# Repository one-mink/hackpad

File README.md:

# Hackpad
A macropad.

CAD

Schematics

PCB

Case

BOM:
    5x Cherry MX Switches
    5x DSA Keycaps
    2x WS2812B LEDs
    2x EC11 Rotary Encoder
    1x XIAO RP2040
    1x Case (2 printed parts)
    4x M3x5mx4mm heatset inserts

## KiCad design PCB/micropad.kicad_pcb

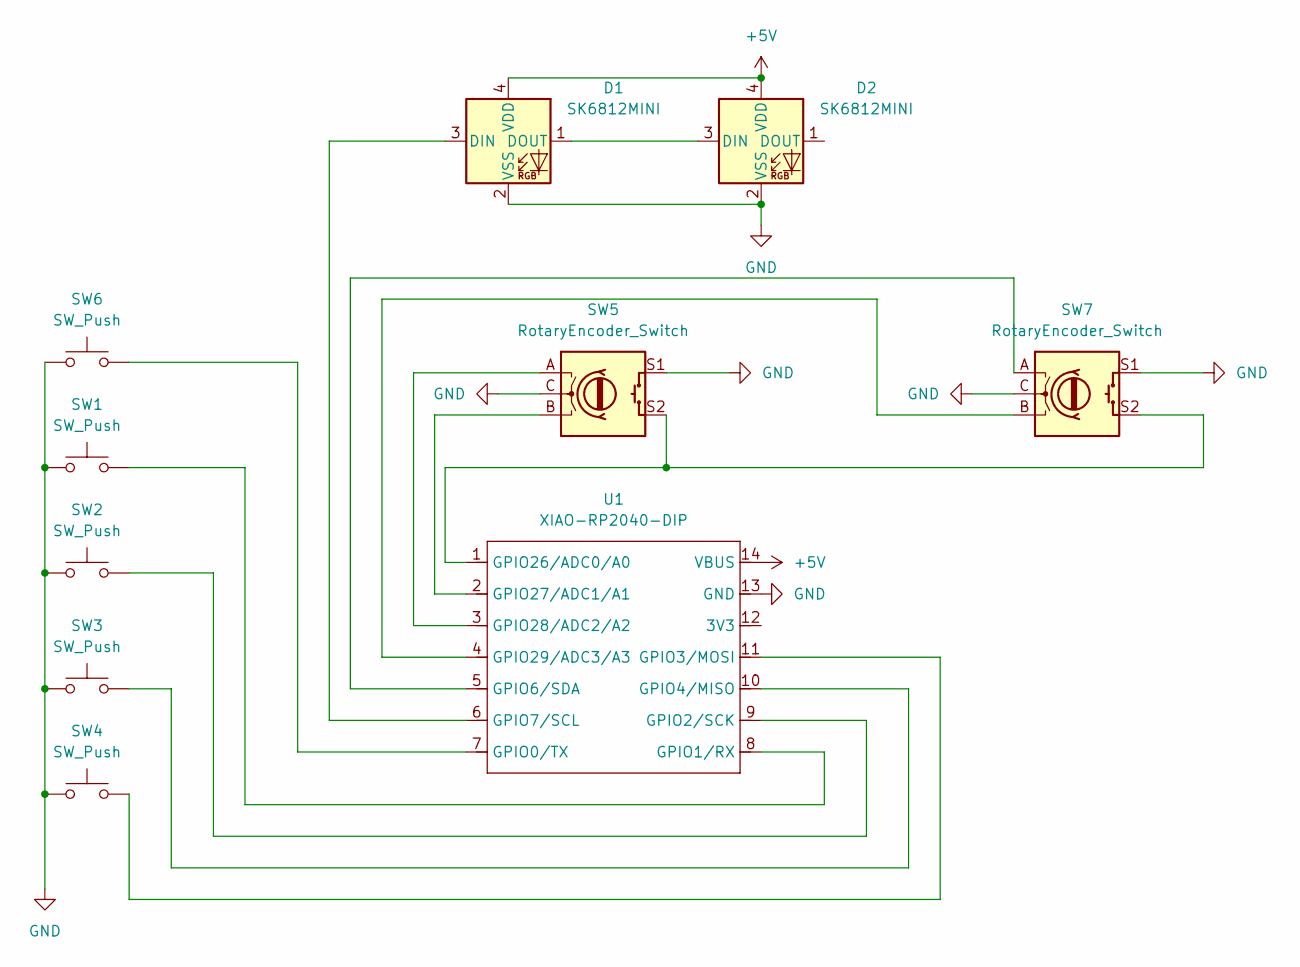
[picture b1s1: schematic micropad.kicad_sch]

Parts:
D1, D2: SK6812MINI; LED_SK6812MINI_PLCC4_3.5x3.5mm_P1.75mm
SW1, SW2, SW3, SW4, SW6: SW_Push; SW_Cherry_MX_1.00u_PCB
SW5, SW7: RotaryEncoder_Switch; RotaryEncoder_Alps_EC11E-Switch_Vertical_H20mm
U1: XIAO-RP2040-DIP

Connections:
+5V: D1.4 (VDD), D2.4 (VDD), U1.14 (VBUS)
GND: D1.2 (VSS), D2.2 (VSS), SW1.1, SW2.1, SW3.1, SW4.1, SW5.C, SW5.S1, SW6.1, SW7.C, SW7.S1, U1.13 (GND)
unnamed: D1.3 (DIN), U1.6 (GPIO7/SCL)
unnamed: D1.1 (DOUT), D2.3 (DIN)
unnamed: SW6.2, U1.7 (GPIO0/TX)
unnamed: SW1.2, U1.8 (GPIO1/RX)
unnamed: SW2.2, U1.9 (GPIO2/SCK)
unnamed: SW4.2, U1.11 (GPIO3/MOSI)
unnamed: SW3.2, U1.10 (GPIO4/MISO)
unnamed: SW7.A, U1.5 (GPIO6/SDA)
unnamed: SW5.S2, SW7.S2, U1.1 (GPIO26/ADC0/A0)
unnamed: SW5.B, U1.2 (GPIO27/ADC1/A1)
unnamed: SW5.A, U1.3 (GPIO28/ADC2/A2)
unnamed: SW7.B, U1.4 (GPIO29/ADC3/A3)

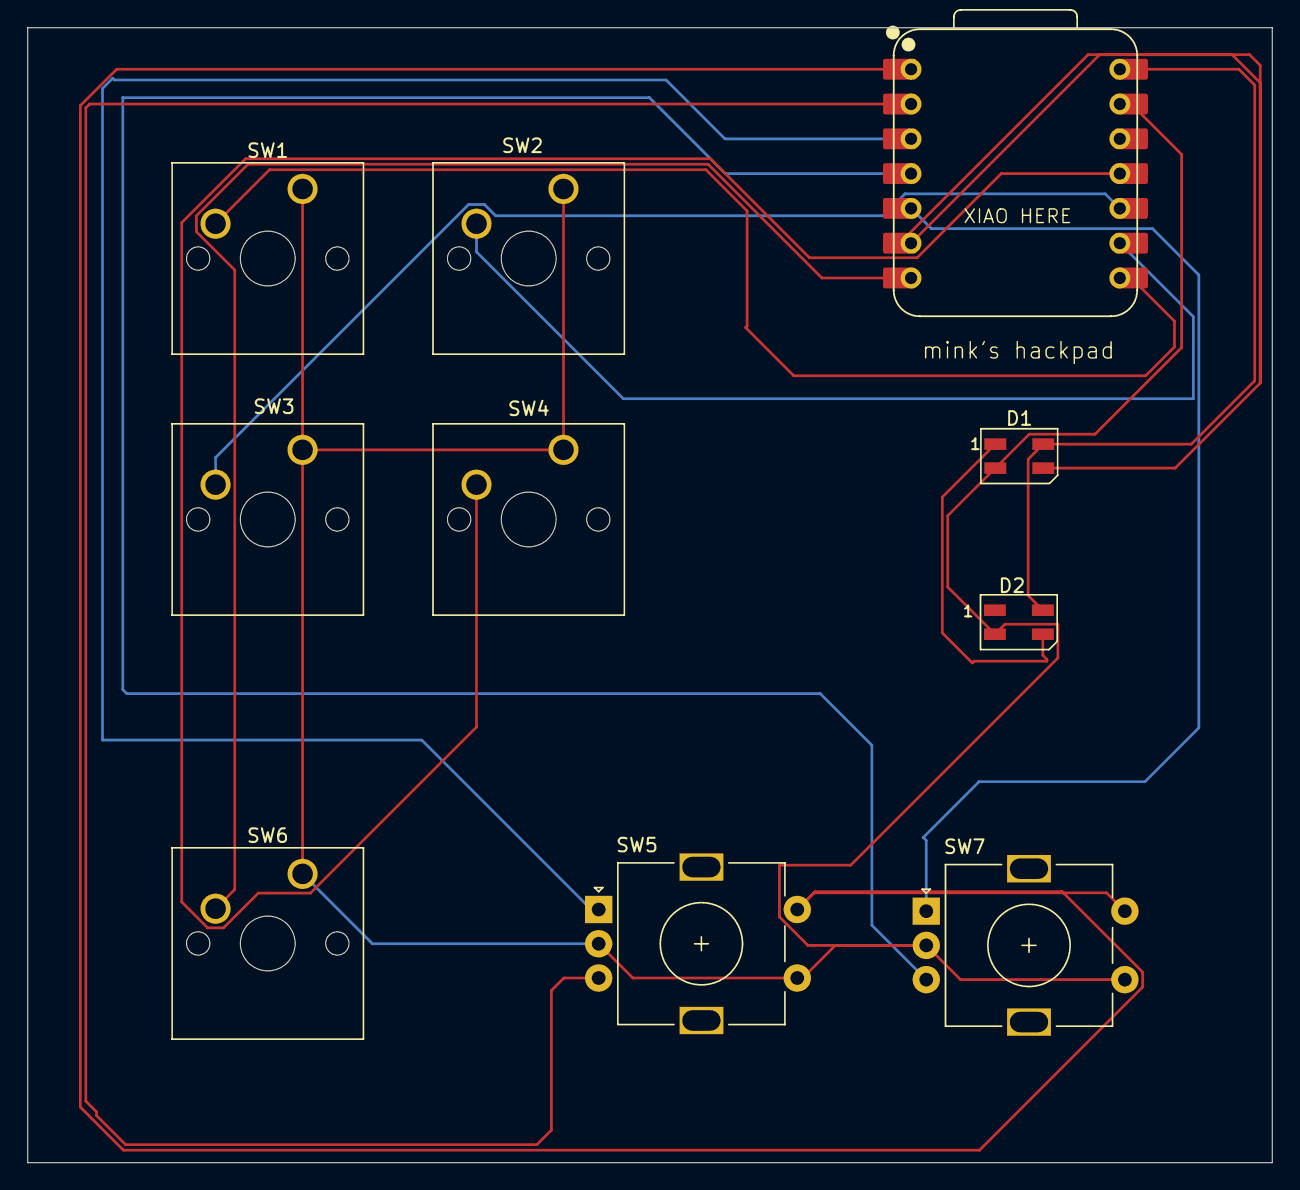
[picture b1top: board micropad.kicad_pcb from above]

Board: 2 copper layers, 90.9 x 82.9 mm, 10 parts (0 on the bottom side), 14 nets.

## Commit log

2025-12-28 Add PCB section with image to README
2025-12-28 Rename project from 'macropad' to 'Hackpad'
2025-12-28 Replace images in README.md
    Updated images for CAD, Schematics, and Case sections.
